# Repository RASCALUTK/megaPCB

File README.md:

# megaPCB
This is a kicad File 

for libraries ask me mdemorat@vols.utk.edu

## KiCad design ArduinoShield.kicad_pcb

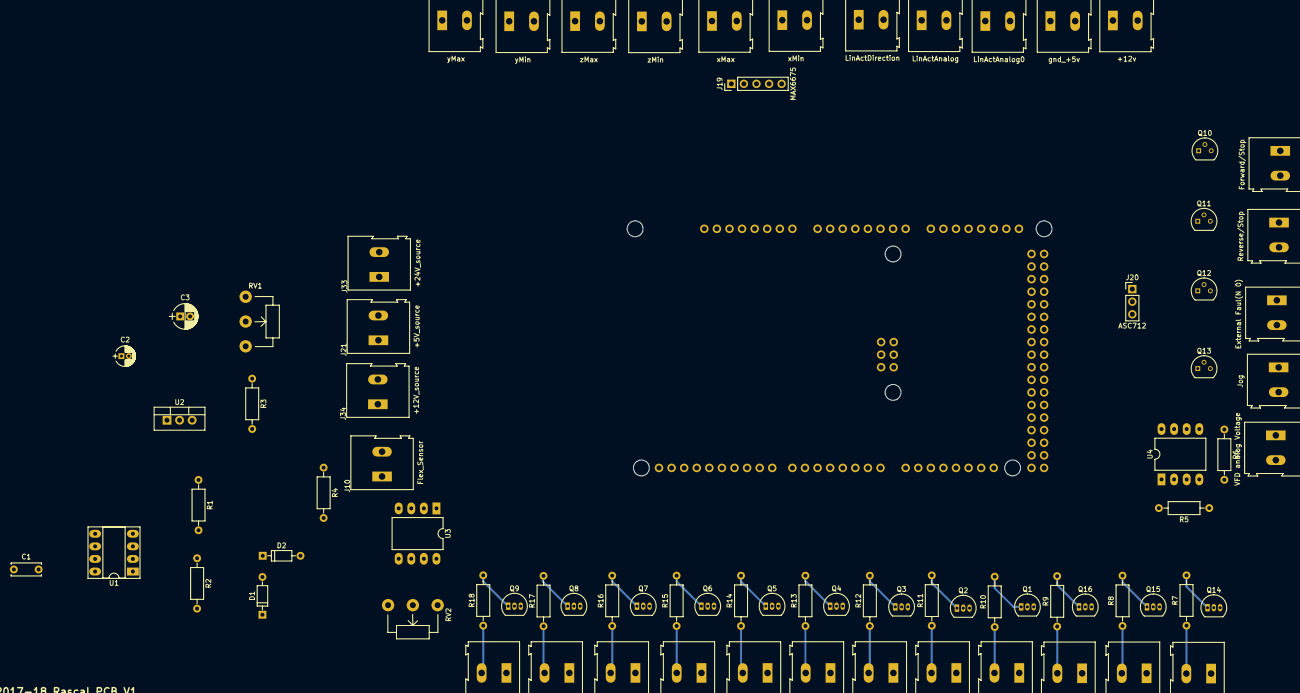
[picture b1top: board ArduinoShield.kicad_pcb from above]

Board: 2 copper layers, 80 parts (1 on the bottom side), 46 nets.

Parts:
C1: C; C_Disc_D6.0mm_W2.5mm_P5.00mm
C2: CP; CP_Radial_D4.0mm_P1.50mm
C3: CP; CP_Radial_D5.0mm_P2.00mm
D1, D2: D; D_DO-35_SOD27_P7.62mm_Horizontal
J1: pulX1; TerminalBlock_Altech_AK300-2_P5.00mm
J2: dirX1; TerminalBlock_Altech_AK300-2_P5.00mm
J3: enaX1; TerminalBlock_Altech_AK300-2_P5.00mm
J4: pulY; TerminalBlock_Altech_AK300-2_P5.00mm
J5: dirY; TerminalBlock_Altech_AK300-2_P5.00mm
J6: enaY; TerminalBlock_Altech_AK300-2_P5.00mm
J7: pulZ; TerminalBlock_Altech_AK300-2_P5.00mm
J8: dirZ; TerminalBlock_Altech_AK300-2_P5.00mm
J9: enaZ; TerminalBlock_Altech_AK300-2_P5.00mm
J10: Flex_Sensor; TerminalBlock_Altech_AK300-2_P5.00mm
J11: VFD analog Voltage; TerminalBlock_Altech_AK300-2_P5.00mm
J12: Forward/Stop; TerminalBlock_Altech_AK300-2_P5.00mm
J13: Jog; TerminalBlock_Altech_AK300-2_P5.00mm
J14: External Faul(N 0); TerminalBlock_Altech_AK300-2_P5.00mm
J15: Reverse/Stop; TerminalBlock_Altech_AK300-2_P5.00mm
J16: pulX0; TerminalBlock_Altech_AK300-2_P5.00mm
J17: dirX0; TerminalBlock_Altech_AK300-2_P5.00mm
J18: enaX0; TerminalBlock_Altech_AK300-2_P5.00mm
J19: MAX6675; Socket_Strip_Straight_1x05_Pitch2.54mm
J20: ASC712; Socket_Strip_Straight_1x03_Pitch2.54mm
J21: +5V_source; TerminalBlock_Altech_AK300-2_P5.00mm
J22: xMin; TerminalBlock_Altech_AK300-2_P5.00mm
J23: xMax; TerminalBlock_Altech_AK300-2_P5.00mm
J24: gnd_+5v; TerminalBlock_Altech_AK300-2_P5.00mm
J25: zMax; TerminalBlock_Altech_AK300-2_P5.00mm
J26: yMin; TerminalBlock_Altech_AK300-2_P5.00mm
J27: yMax; TerminalBlock_Altech_AK300-2_P5.00mm
J28: +12v; TerminalBlock_Altech_AK300-2_P5.00mm
J29: LinActAnalog; TerminalBlock_Altech_AK300-2_P5.00mm
J30: LinActAnalog0; TerminalBlock_Altech_AK300-2_P5.00mm
J31: LinActDirection; TerminalBlock_Altech_AK300-2_P5.00mm
J32: zMin; TerminalBlock_Altech_AK300-2_P5.00mm
J33: +24V_source; TerminalBlock_Altech_AK300-2_P5.00mm
J34: +12V_source; TerminalBlock_Altech_AK300-2_P5.00mm
Q1, Q2, Q3, Q4, Q5, Q6, Q7, Q8, Q9, Q14, Q15, Q16: Q_NPN_CBE; TO-92_Inline_Narrow_Oval
Q10, Q11, Q12, Q13: PN2222A; TO-92_Molded_Narrow
R1, R2, R3, R4, R5, R6, R7, R8, R9, R10, R11, R12, R13, R14, R15, R16, R17, R18: R; R_Axial_DIN0207_L6.3mm_D2.5mm_P10.16mm_Horizontal
RV1, RV2: POT; Potentiometer_WirePads_largePads
U1: NE555; DIP-8_W7.62mm_Socket_LongPads
U2: LM337_TO220; TO-220-3_Vertical
U3: MCP6004; DIP-8_W10.16mm_LongPads
U4: LM741; DIP-8_W10.16mm_LongPads
XA1: Arduino_Mega2560_Shield

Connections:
+5V: J1.1, J2.1, J3.1, J4.1, J5.1, J6.1, J7.1, J8.1, J9.1, J16.1, J17.1, J18.1, J19.2, J20.3, J21.1, J22.1, J23.1, J24.2, J25.1, J26.1, J27.1, J29.1, J32.1, XA1.5V1, XA1.5V3, XA1.5V4
+12V: J28.2, J34.1, R1.1, U1.4, U1.8, U4.7, XA1.VIN
/force/forceOut: RV2.1, RV2.2, U3.1, XA1.A0
/linearAct/linActAnalog: J29.2, J30.1
GND: C1.2, C2.2, D1.1, J11.2, J19.1, J20.1, J21.2, J24.1, J28.1, J30.2, J33.2, J34.2, Q1.3, Q2.3, Q3.3, Q4.3, Q5.3, Q6.3, Q7.3, Q8.3, Q9.3, Q14.3, Q15.3, Q16.3, R5.1, U1.1, U3.3, U3.4, U4.4, XA1.GND1, XA1.GND2, XA1.GND3, XA1.GND5, XA1.GND6
unnamed: C1.1, U1.5
unnamed: C2.1, R2.2, U1.2, U1.6
unnamed: C3.1, D1.2, D2.1
unnamed: C3.2, U1.3
unnamed: RV1.2, RV1.3
unnamed: D2.2, U2.2
unnamed: J10.1, RV2.3, U3.2
unnamed: J10.2, R4.2
unnamed: R3.2, R4.1, U2.3
unnamed: J1.2, R10.1
unnamed: J2.2, R11.1
unnamed: J3.2, R12.1
unnamed: J4.2, R13.1
unnamed: J5.2, R14.1
unnamed: J6.2, R15.1
unnamed: J7.2, R16.1
unnamed: J8.2, R17.1
unnamed: J9.2, R18.1
unnamed: J11.1, R6.1, U4.6
unnamed: J12.1, Q10.3
unnamed: J12.2, J13.2, J14.2, J15.2, Q10.1, Q11.1, Q12.1, Q13.1, R5.2, R6.2, U4.2
unnamed: J13.1, Q13.3
unnamed: J14.1, Q12.3
unnamed: J15.1, Q11.3
unnamed: J16.2, R7.1
unnamed: J17.2, R8.1
unnamed: J18.2, R9.1
unnamed: Q1.1, R10.2
unnamed: Q2.1, R11.2
unnamed: Q3.1, R12.2
unnamed: Q4.1, R13.2
unnamed: Q5.1, R14.2
unnamed: Q6.1, R15.2
unnamed: Q7.1, R16.2
unnamed: Q8.1, R17.2
unnamed: Q9.1, R18.2
unnamed: Q14.1, R7.2
unnamed: Q15.1, R8.2
unnamed: Q16.1, R9.2
unnamed: R1.2, R2.1, U1.7
unnamed: R3.1, RV1.1, U2.1
